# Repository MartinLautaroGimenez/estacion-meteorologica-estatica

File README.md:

# Estación Meteorológica Fija
## ¿Qué es una estación meteorológica?
Una estación meteorológica es un dispositivo tecnológico de características electrónica e informática que permite nuclear parámetros relevantes para realizar estudios y sacar conclusiones frente a fenómenos físicos.

## ¿Qué es E.M.F.?
Este es el inicio del proyecto EME, fue desarrollado en 2022 por el Alumno Nicolas Pérez de la escuela ETec UM, para posteriormente en el año 2024, tras el egreso de Nicolas de la escuela, la estación fue acogida por el taller Aeroglobe ETec y en conjunto con el nevo equipo que se creó en el taller se le pudo dar continuidad y agregar sensores y actualizar partes de la estación. 

## E.M.E.
Este es un proyecto institucional y surge de la necesidad de poder comprar los sistemas atmosféricos de algunos departamentos como Godoy Cruz, Gran Mendoza, Lavalle entre otros departamentos unidos a la red de la Escuela ETec de la Universidad de Mendoza para tener un conocimiento amplio de las condiciones atmosféricas de la provincia y así contribuir al análisis de las condiciones climáticas de la misma. Este es el nexo entre todas las estaciones y su finalidad es crear una red de nodos open surce en la cual podamos extraer datos para diferentes investigaciones o proyectos ya sean de la escuela o externos ya que los datos son públicos.  

## Los modulos incorporados
  - [ESP32](#ESP32)
  - [BMP180](#BMP180)
  - [DHT22](#DHT22)
  - [BMS 3S](#BMS-3S)
  - [Baterías 18650](#Baterías-18650)
  - [Panel Solar](#Panel-Solar)
  - [Sensor de Hoja Mojada](#Sensor-de-Hoja-Mojada)
  - [BH1750](#BH1750)
  - [MQ-135](#MQ-135)
  - [Veleta](#Veleta)
  - [Anemómetro](#Anemómetro)
 
### ESP32
#### DOIT ESP32 Devkit V1
La placa ESP32 (DOIT ESP32 Devkit V1) es un módulo basado en el microcontrolador ESP32, conocido por su capacidad de conexión Wi-Fi y Bluetooth. En nuestra estación meteorológica, esta placa desempeñará un papel vital al ofrecer una base solida para la  recopilación y transmisión de datos ambientales. Con su capacidad para manejar múltiples sensores y su compatibilidad con entornos de desarrollo como Arduino IDE, la ESP32 garantiza un funcionamiento continuo incluso en condiciones adversas, asegurando la integridad y precisión de las mediciones meteorológicas.

<div align="center">
   
</div>

### BMP180
El sensor BMP180 es un dispositivo el cual es utilizado para medir la presión atmosférica y la altitud a nivel del mar con un alto nivel de precisión. Es conocido por su pequeño tamaño y por su simplicidad al momento de realizar mediciones. 

<div align="center">
   
</div>

### DHT22
El sensor DHT22 es un componente crucial en el campo de la electrónica y la monitorización ambiental. 
Su función principal es medir con precisión la temperatura ambiente y la humedad relativa del entorno en el que se encuentra la estación meteorológica. Este sensor incorpora un termistor para la medición de la temperatura y un elemento especializado para medir la humedad relativa.

<div align="center">
   
</div>

### BMS 3S
El módulo BMS 3S es esencial para la carga de las baterías, ya que desempeña un papel crucial en la regulación del voltaje que reciben durante el proceso de carga. Este módulo garantiza que las baterías reciban el voltaje adecuado para una carga segura y eficiente.

<div align="center">
   
</div>

### Baterías 18650
Las baterías 18650 son células recargables de iones de litio conocidas por su alta densidad de energía y fiabilidad. En nuestra estación meteorológica, estas baterías desempeñarán un papel vital al ofrecer una fuente de alimentación constante y duradera, lo que garantizará un funcionamiento continuo incluso en condiciones adversas en las que el panel solar no pueda suministrar la potencia nominal.

<div align="center">
   
</div>

### Panel Solar
El panel solar le da la capacidad de poder estar lejos en un sector en donde no sea posible el tendido eléctrico para la alimentación de la EME, además brinda una opción de energía sustentable y limpia, reduciendo así el consumo eléctrico convencional que mayoritariamente proviene de centrales térmicas.
Además el mismo se le incorpora un pequeño módulo regulador de tensión para poder adaptar los niveles de tensión requeridos para la lógica del microcontrolador.

<div align="center">
   
</div>

### Sensor de Hoja Mojada
El sensor de hoja mojada permite tomar cómo parámetro el estado de la planta en cuanto a la generación de microorganismos que se presenten en la planta, de está manera se puede regular la aplicación de insecticida sin sobredosificar y ahorrando cantidades del mismo, si el mismo fuese aplicado a calendario. Además permite tener un mejor control en cuanto a la biodiversidad de los demás microorganismos que puedan aparecer en la planta que no sean dañinos. 

<div align="center">
   
</div>

### BH1750
El sensor BH1750 es un sensor el cual está diseñado para medir la intensidad de la luz de manera precisa. Es altamente valorado por su facilidad de uso y su capacidad de obtener lecturas rápidas en una amplia variedad de ambientes. Su pequeño tamaño y alta precisión lo hacen el más querido de los sensores de luz.

<div align="center">
   
</div>

### MQ-135
El sensor MQ135 es un componente el cual permite detectar gases nocivos para el aire, como el amoníaco, sulfuro de hidrógeno, dióxido de carbono, y otros compuestos orgánicos volátiles. Es conocido por la capacidad de proporcionar alertas tempranas sobre la presencia de estos gases.
De este sensor podemos tomar datos analógicos del comportamiento de la mezcla de gases y la capacidad de marcar un umbral de disparo para una salida digital de ser requerida, para ello es necesario acceder manualmente al trimmer de su pcb y calibrar el disparo del mismo

<div align="center">
   
</div>

### Veleta
Permite tomar la dirección actual del viento discretizando dicha dirección en 8 posiciones cardinales gracias a su forma constructiva, un imán de neodimio y 8 reed switch.

<div align="center">
     
</div>

### Anemómetro 
Para el anemómetro se requiere tanto de la parte física como del módulo o sensor de efecto hall que es quien detecta cada revolución de giro y la envía a una etapa amplificadora para poder contar cada pulso entrante 

<div align="center">
    
</div>

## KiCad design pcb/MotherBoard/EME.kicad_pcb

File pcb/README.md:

# Circuito
Para el diseño del proyecto, concretamente para la parte electrónica de diseño de PCB se a optado por usar un software libre y poderoso llamado KiCAD en su versión número 7 con la integración de una librería casera tanto el símbolo esquemático cómo la huella (footprint) del PCB.

# Diagrama esquemático

Para el diagrama 

# Diseño de la PCB

Para el Diseño de la PCB

# Modelo 3D

Para el modelo 3D

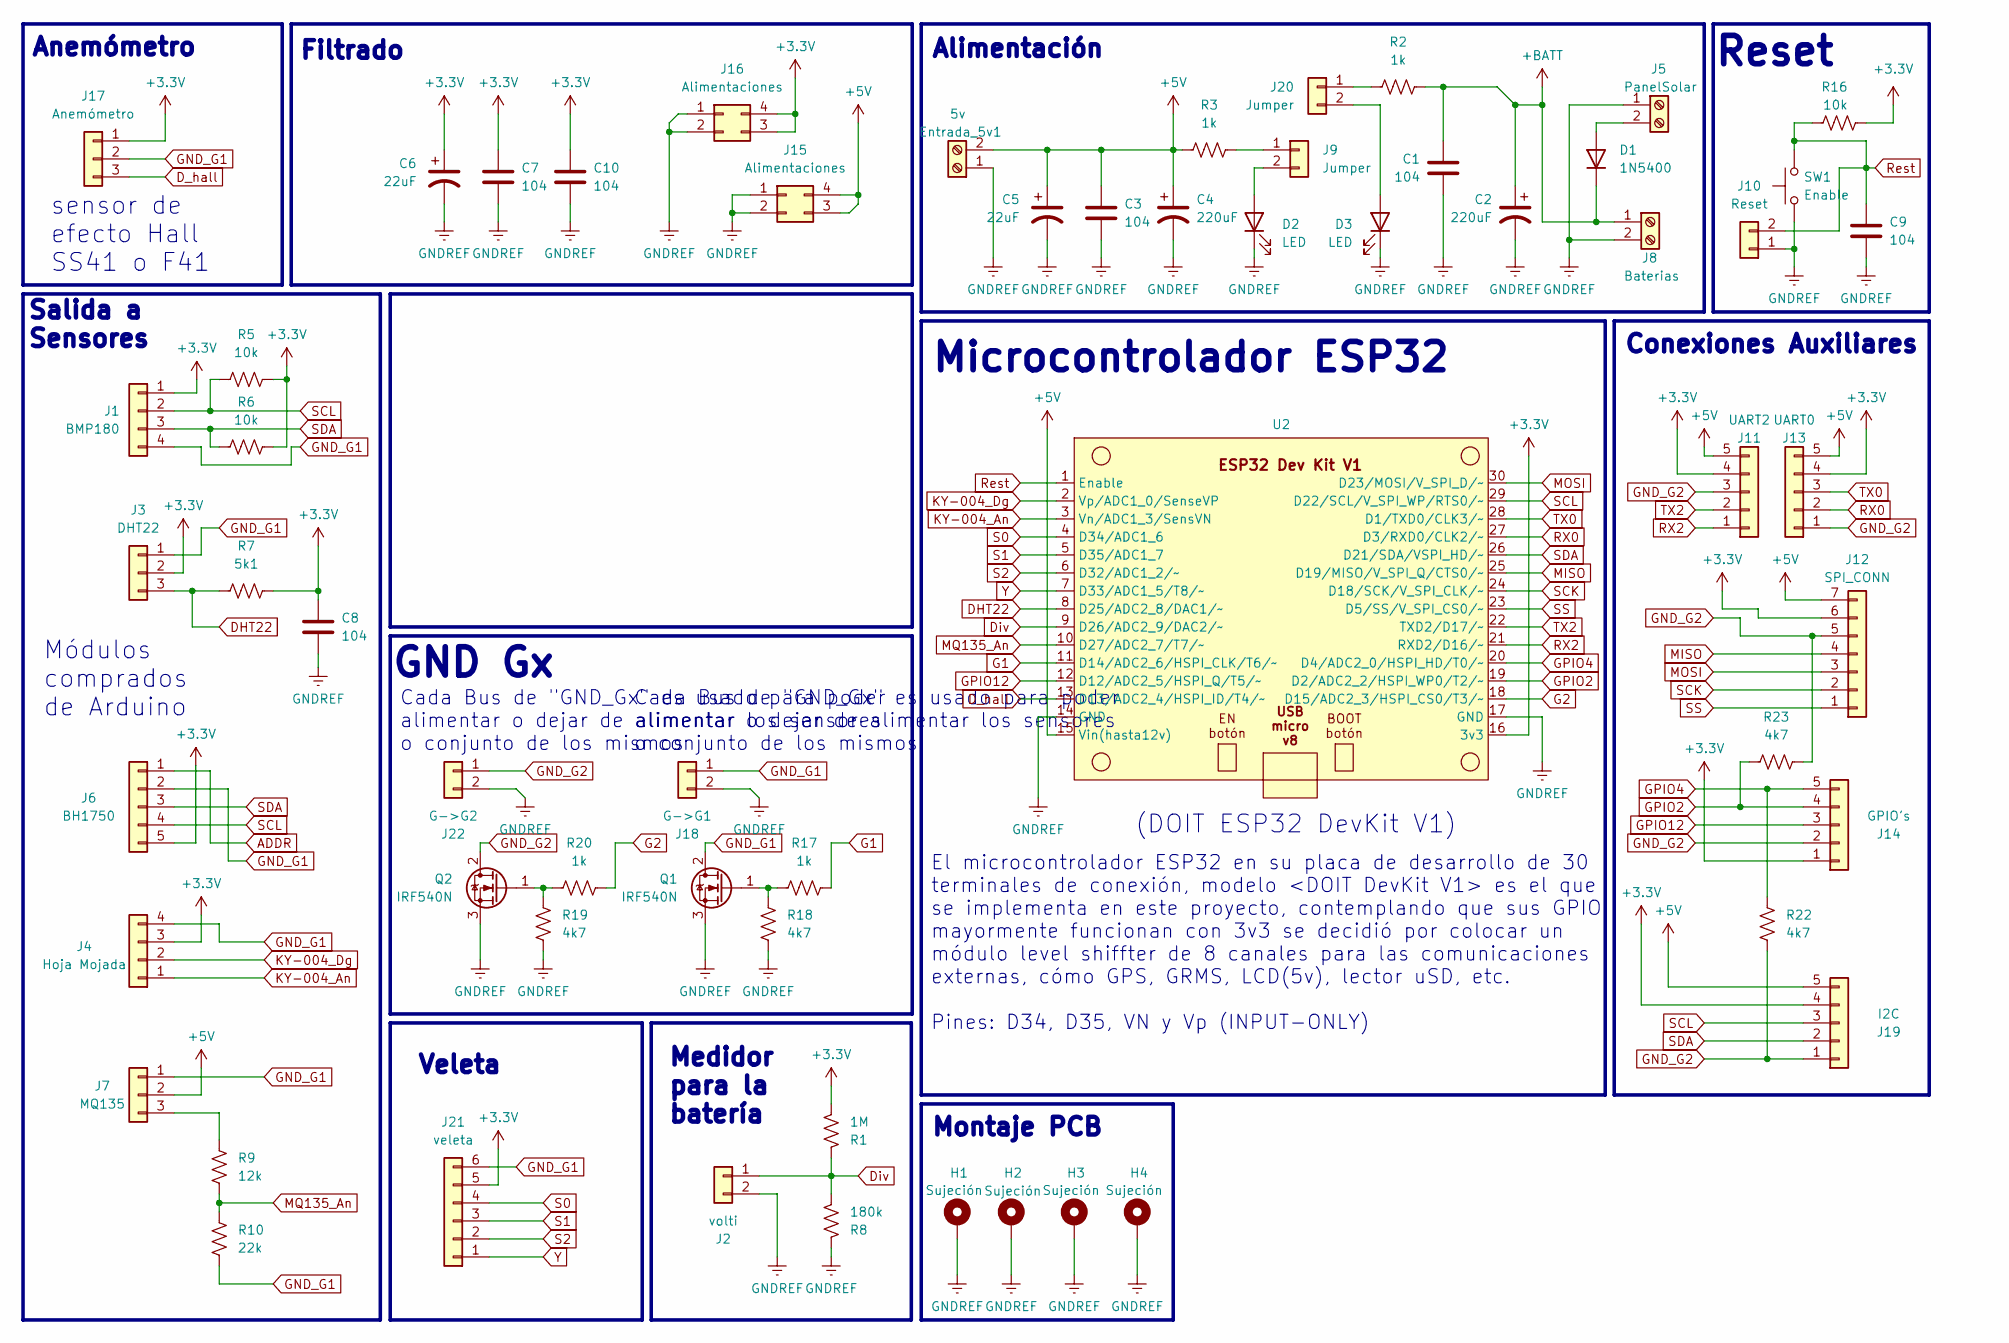
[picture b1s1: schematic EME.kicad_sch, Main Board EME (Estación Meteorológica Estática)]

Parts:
C1, C3, C7, C10: 104; C_Disc_D7.0mm_W2.5mm_P5.00mm
C2, C4: 220uF; C_Radial_D8.0mm_H11.5mm_P3.50mm
C5, C6: 22uF; C_Radial_D8.0mm_H7.0mm_P3.50mm
C8: 104; C_Disc_D7.5mm_W4.4mm_P5.00mm
C9: 104; C_Disc_D4.3mm_W1.9mm_P5.00mm
D1: 1N5400; D_DO-201AD_P15.24mm_Horizontal
D2, D3: LED; LED_D5.0mm_Clear
Entrada_5v1: 5v; TerminalBlock_Phoenix_PT-1,5-2-5.0-H_1x02_P5.00mm_Horizontal
H1, H2, H3, H4: Sujeción; MountingHole_3.5mm_Pad
J1: BMP180; PinHeader_1x04_P2.54mm_Vertical
J2: volti; PinHeader_1x02_P2.54mm_Vertical
J3: DHT22; PinHeader_1x03_P2.54mm_Vertical
J4: Hoja Mojada; PinHeader_1x04_P2.54mm_Vertical
J5: PanelSolar; TerminalBlock_Phoenix_PT-1,5-2-5.0-H_1x02_P5.00mm_Horizontal
J6: BH1750; PinHeader_1x05_P2.54mm_Vertical
J7: MQ135; PinHeader_1x03_P2.54mm_Vertical
J8: Baterias; TerminalBlock_Phoenix_PT-1,5-2-5.0-H_1x02_P5.00mm_Horizontal
J9, J20: Jumper; PinHeader_1x02_P2.54mm_Vertical
J10: Reset; PinHeader_1x02_P2.54mm_Vertical
J11: UART2; PinHeader_1x05_P2.54mm_Vertical
J12: SPI_CONN; PinHeader_1x07_P2.54mm_Vertical
J13: UART0; PinHeader_1x05_P2.54mm_Vertical
J14: GPIO's; PinHeader_1x05_P2.54mm_Vertical
J15, J16: Alimentaciones; PinHeader_2x02_P2.54mm_Vertical
J17: Anemómetro; PinHeader_1x03_P2.54mm_Vertical
J18: G->G1; PinHeader_1x02_P2.54mm_Vertical
J19: I2C; PinHeader_1x05_P2.54mm_Vertical
J21: veleta; PinHeader_1x06_P2.54mm_Vertical
J22: G->G2; PinHeader_1x02_P2.54mm_Vertical
Q1, Q2: IRF540N; TO-220-3_Vertical
R1: 1M; R_Axial_DIN0207_L6.3mm_D2.5mm_P10.16mm_Horizontal
R2, R3, R17, R20: 1k; R_Axial_DIN0207_L6.3mm_D2.5mm_P10.16mm_Horizontal
R5, R6, R16: 10k; R_Axial_DIN0207_L6.3mm_D2.5mm_P10.16mm_Horizontal
R7: 5k1; R_Axial_DIN0207_L6.3mm_D2.5mm_P10.16mm_Horizontal
R8: 180k; R_Axial_DIN0207_L6.3mm_D2.5mm_P10.16mm_Horizontal
R9: 12k; R_Axial_DIN0207_L6.3mm_D2.5mm_P10.16mm_Horizontal
R10: 22k; R_Axial_DIN0207_L6.3mm_D2.5mm_P10.16mm_Horizontal
R18, R19, R22, R23: 4k7; R_Axial_DIN0207_L6.3mm_D2.5mm_P10.16mm_Horizontal
SW1: Enable; SW_PUSH_6mm_H8mm
U2: ESP32-DevKit_V1

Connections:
+3.3V: C6.1, C7.1, C8.1, C10.1, J1.1, J3.2, J4.3, J6.5, J11.4, J12.6, J13.4, J14.1, J16.3, J16.4, J17.1, J19.4, J21.5, R1.1, R5.2, R6.2, R7.2, R16.2, U2.16 (3v3); also elsewhere on the board
+5V: C3.1, C4.1, C5.1, Entrada_5v1.2, J7.2, J11.5, J12.7, J13.5, J15.3, J15.4, J19.5, R3.1, U2.15 (Vin(hasta12v))
+BATT: C1.1, C2.1, D1.1 (K), J8.1, R2.2
ADDR: J6.1
DHT22: J3.3, R7.1, U2.8 (D25/ADC2_8/DAC1/~)
D_hall: J17.3, U2.13 (D13/ADC2_4/HSPI_ID/T4/~)
Div: J2.1, R1.2, R8.1, U2.9 (D26/ADC2_9/DAC2/~)
G1: R17.2, U2.11 (D14/ADC2_6/HSPI_CLK/T6/~)
G2: R20.2, U2.18 (D15/ADC2_3/HSPI_CS0/T3/~)
GNDREF: C1.2, C2.2, C3.2, C4.2, C5.2, C6.2, C7.2, C8.2, C9.2, C10.2, D2.1 (K), D3.1 (K), Entrada_5v1.1, H1.1, H2.1, H3.1, H4.1, J2.2, J5.1, J8.2, J10.1, J15.1, J15.2, J16.1, J16.2, J18.2, J22.2, Q1.3 (S), Q2.3 (S), R8.2, R18.1, R19.1, SW1.1, U2.14 (GND), U2.17 (GND); also elsewhere on the board
GND_G1: J1.4, J3.1, J4.4, J6.2, J7.1, J17.2, J18.1, J21.6, Q1.2 (D), R10.1
GND_G2: J11.3, J12.5, J13.1, J14.2, J19.1, J22.1, Q2.2 (D), R22.1, R23.1
GPIO2: J14.4, R23.2, U2.19 (D2/ADC2_2/HSPI_WP0/T2/~)
GPIO4: J14.5, R22.2, U2.20 (D4/ADC2_0/HSPI_HD/T0/~)
GPIO12: J14.3, U2.12 (D12/ADC2_5/HSPI_Q/T5/~)
KY-004_An: J4.1, U2.3 (Vn/ADC1_3/SensVN)
KY-004_Dg: J4.2, U2.2 (Vp/ADC1_0/SenseVP)
MISO: J12.4, U2.25 (D19/MISO/V_SPI_Q/CTS0/~)
MOSI: J12.3, U2.30 (D23/MOSI/V_SPI_D/~)
MQ135_An: R9.1, R10.2, U2.10 (D27/ADC2_7/T7/~)
unnamed: D1.2 (A), J5.2
unnamed: D2.2 (A), J9.2
unnamed: D3.2 (A), J20.2
unnamed: J7.3, R9.2
unnamed: J9.1, R3.2
unnamed: J20.1, R2.1
unnamed: Q1.1 (G), R17.1, R18.2
unnamed: Q2.1 (G), R19.2, R20.1
RX0: J13.2, U2.27 (D3/RXD0/CLK2/~)
RX2: J11.1, U2.21 (RXD2/D16/~)
Rest: C9.1, J10.2, R16.1, SW1.2, U2.1 (Enable)
S0: J21.4, U2.4 (D34/ADC1_6)
S1: J21.3, U2.5 (D35/ADC1_7)
S2: J21.2, U2.6 (D32/ADC1_2/~)
SCK: J12.2, U2.24 (D18/SCK/V_SPI_CLK/~)
SCL: J1.2, J6.4, J19.3, R5.1, U2.29 (D22/SCL/V_SPI_WP/RTS0/~)
SDA: J1.3, J6.3, J19.2, R6.1, U2.26 (D21/SDA/VSPI_HD/~)
SS: J12.1, U2.23 (D5/SS/V_SPI_CS0/~)
TX0: J13.3, U2.28 (D1/TXD0/CLK3/~)
TX2: J11.2, U2.22 (TXD2/D17/~)
Y: J21.1, U2.7 (D33/ADC1_5/T8/~)

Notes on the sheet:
Cada Bus de "GND_Gx" es usado para poder alimentar o dejar de alimentar los sensores o conjunto de los mismos
Salida a Sensores
GND Gx
Anemómetro
sensor de efecto Hall SS41 o F41
El microcontrolador ESP32 en su placa de desarrollo de 30 terminales de conexión, modelo <DOIT DevKit V1> es el que se implementa en este proyecto, contemplando que sus GPIO mayormente funcionan con 3v3 se decidió por colocar un módulo level shiffter de 8 canales para las comunicaciones externas, c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
Microcontrolador ESP32
Medidor para la batería
Veleta
Módulos comprados de Arduino
Reset
Alimentación
Montaje PCB
Filtrado
(DOIT ESP32 DevKit V1)
Conexiones Auxiliares

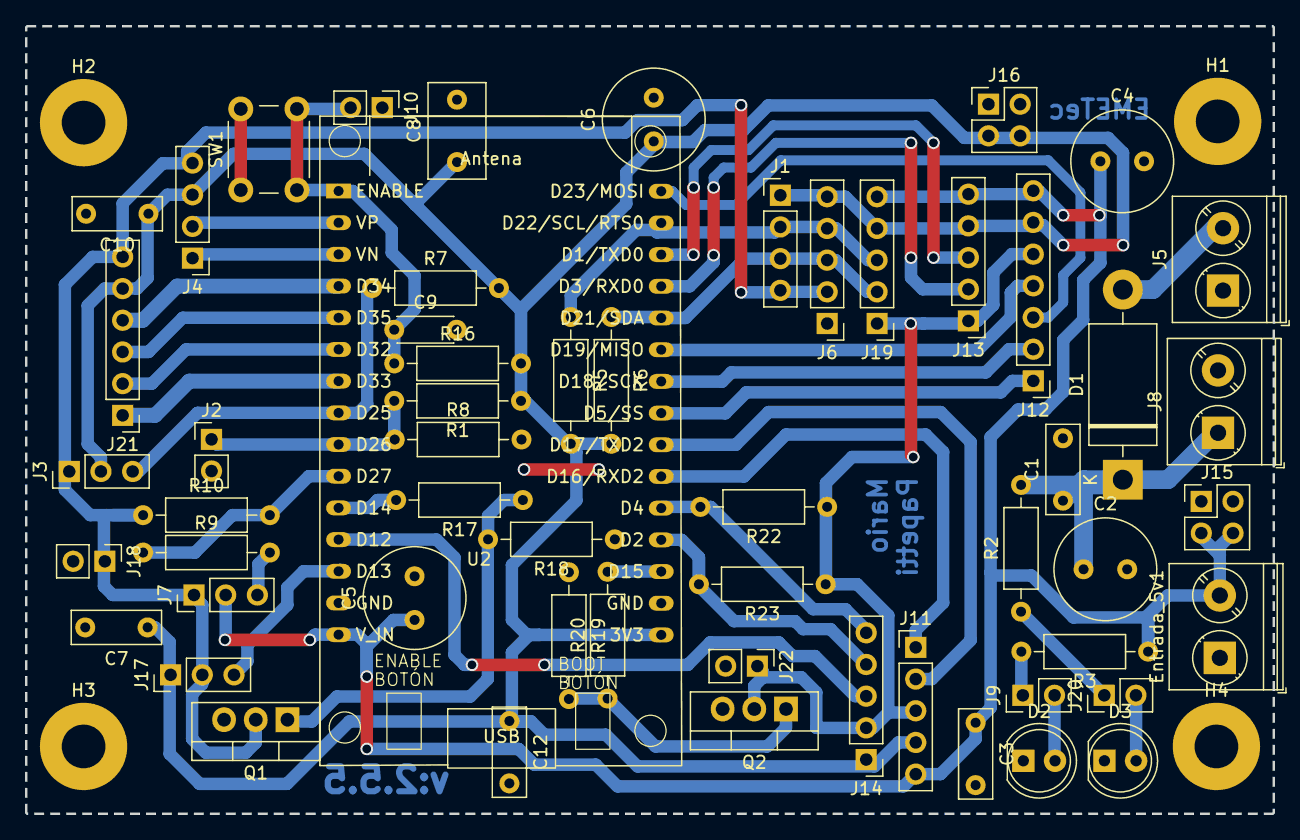
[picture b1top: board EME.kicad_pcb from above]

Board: 2 copper layers, 100.0 x 63.1 mm, 61 parts (0 on the bottom side), 40 nets.

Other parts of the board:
C12: 104; C_Disc_D7.0mm_W2.5mm_P5.00mm

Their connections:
+3.3V: C12.1; also elsewhere on the board
GNDREF: C12.2; also elsewhere on the board

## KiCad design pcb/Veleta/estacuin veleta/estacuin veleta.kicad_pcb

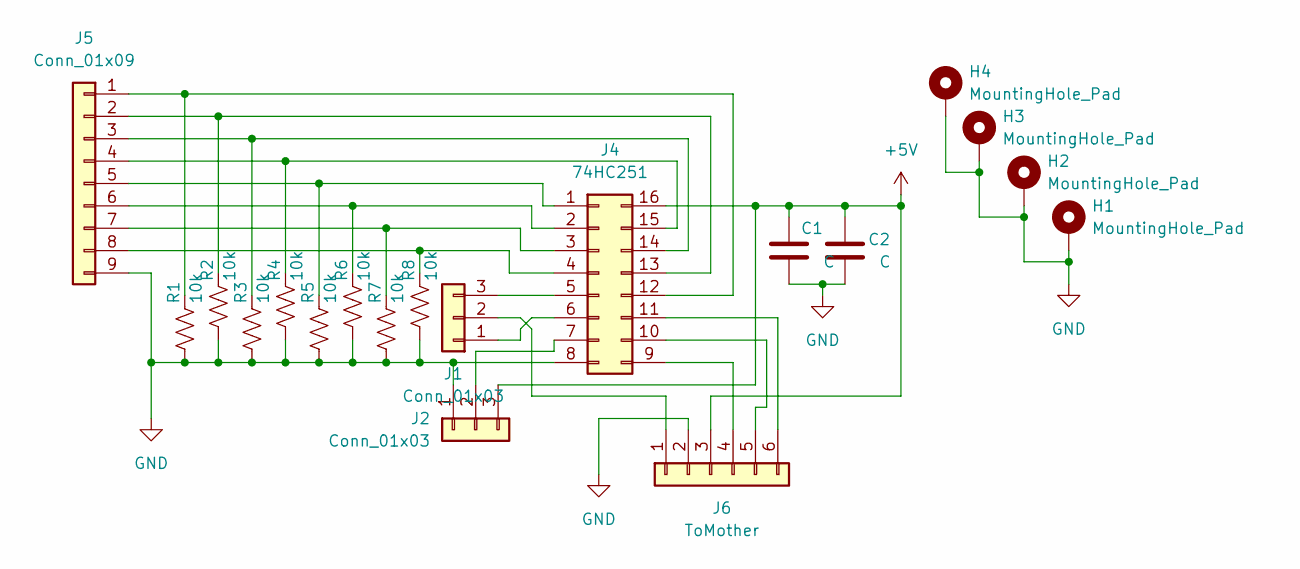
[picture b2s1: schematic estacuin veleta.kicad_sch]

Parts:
C1, C2: C; C_Radial_D6.3mm_H7.0mm_P2.50mm
H1, H2, H3, H4: MountingHole_Pad; MountingHole_2.2mm_M2_DIN965_Pad
J1, J2: Conn_01x03; PinHeader_1x03_P2.54mm_Vertical
J4: 74HC251; DIP-16_W7.62mm
J5: Conn_01x09; PinSocket_1x09_P2.54mm_Vertical
J6: ToMother; PinSocket_1x06_P2.54mm_Vertical
R1, R2, R3, R4, R5, R6, R7, R8: 10k; R_Axial_DIN0207_L6.3mm_D2.5mm_P10.16mm_Horizontal

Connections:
+5V: C1.1, C2.1, J2.3, J4.16, J6.3
GND: C1.2, C2.2, H1.1, H2.1, H3.1, H4.1, J2.1, J4.8, J5.9, J6.2, R1.2, R2.2, R3.2, R4.2, R5.2, R6.2, R7.2, R8.2
unnamed: J1.1, J4.6
unnamed: J1.2, J6.1
unnamed: J1.3, J4.5
unnamed: J2.2, J4.7
unnamed: J4.1, J5.5, R5.1
unnamed: J4.2, J5.6, R6.1
unnamed: J4.3, J5.7, R7.1
unnamed: J4.4, J5.8, R8.1
unnamed: J4.9, J6.4
unnamed: J4.10, J6.5
unnamed: J4.11, J6.6
unnamed: J4.12, J5.1, R1.1
unnamed: J4.13, J5.2, R2.1
unnamed: J4.14, J5.3, R3.1
unnamed: J4.15, J5.4, R4.1

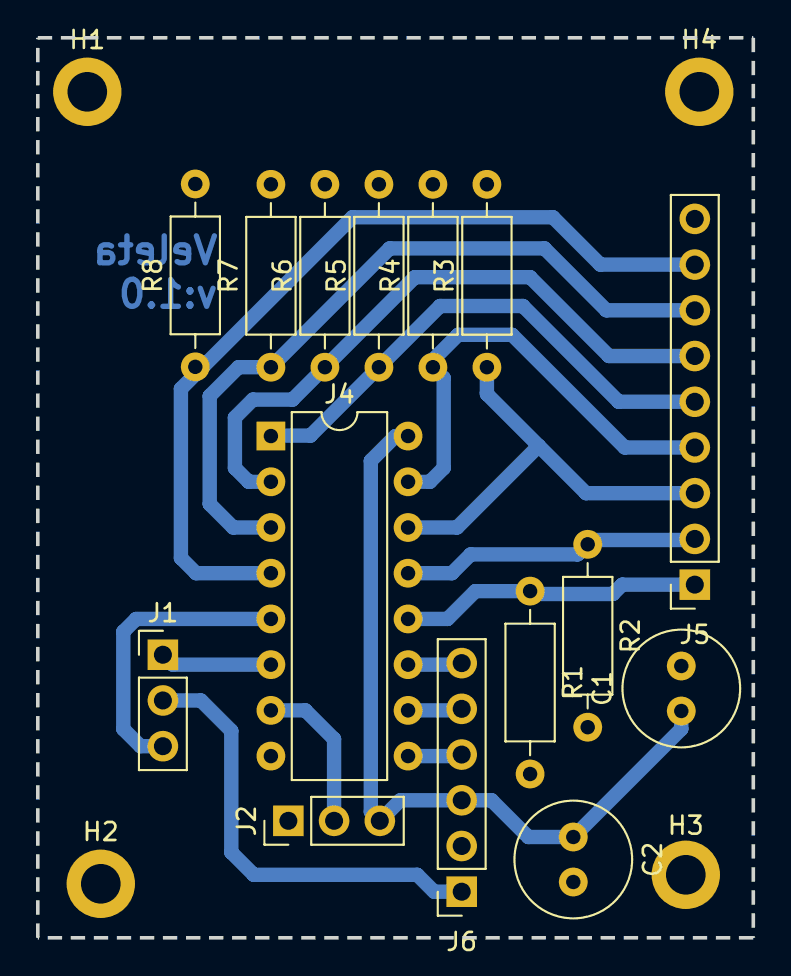
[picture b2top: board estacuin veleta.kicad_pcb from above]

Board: 2 copper layers, 39.8 x 50.0 mm, 19 parts (0 on the bottom side), 17 nets.

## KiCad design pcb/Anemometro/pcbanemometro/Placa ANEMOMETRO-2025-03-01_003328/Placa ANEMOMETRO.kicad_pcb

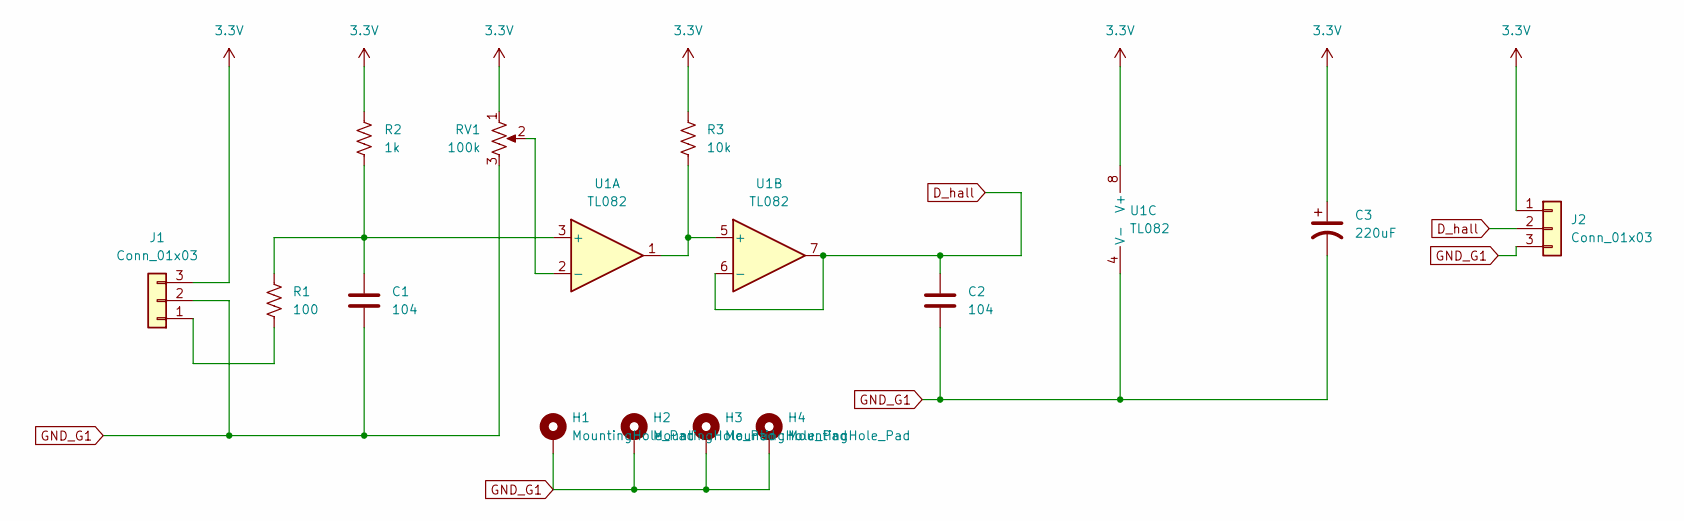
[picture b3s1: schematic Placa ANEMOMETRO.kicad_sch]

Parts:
C1, C2: 104; C_Disc_D4.3mm_W1.9mm_P5.00mm
C3: 220uF; C_Radial_D5.0mm_H7.0mm_P2.00mm
H1, H2, H3, H4: MountingHole_Pad; MountingHole_2.2mm_M2_DIN965_Pad
J1, J2: Conn_01x03; PinHeader_1x03_P2.54mm_Vertical
R1: 100; R_Axial_DIN0207_L6.3mm_D2.5mm_P7.62mm_Horizontal
R2: 1k; R_Axial_DIN0207_L6.3mm_D2.5mm_P7.62mm_Horizontal
R3: 10k; R_Axial_DIN0207_L6.3mm_D2.5mm_P7.62mm_Horizontal
RV1: 100k; Potentiometer_Bourns_3296Y_Vertical
U1: TL082; DIP-8_W7.62mm_Socket

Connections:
3.3V: C3.1, J1.3, J2.1, R2.1, R3.1, RV1.1, U1.8 (V+)
D_hall: C2.1, J2.2, U1.6 (-), U1.7
GND_G1: C1.2, C2.2, C3.2, H1.1, H2.1, H3.1, H4.1, J1.2, J2.3, RV1.3, U1.4 (V-)
unnamed: J1.1, R1.2
unnamed: C1.1, R1.1, R2.2, U1.3 (+)
unnamed: RV1.2, U1.2 (-)
unnamed: R3.2, U1.1, U1.5 (+)

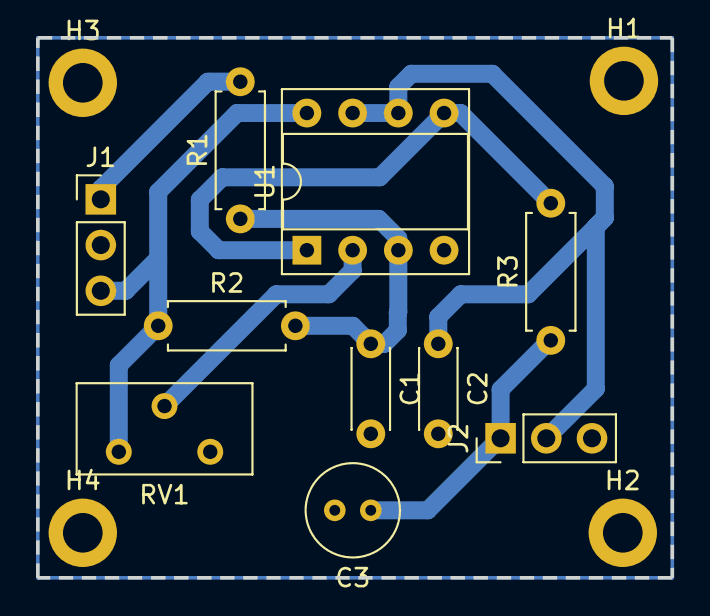
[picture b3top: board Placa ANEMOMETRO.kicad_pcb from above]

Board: 2 copper layers, 35.2 x 30.0 mm, 14 parts (0 on the bottom side), 7 nets.

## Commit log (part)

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2024-03-07 Se añadió nodejs y se añadio un ejemplar de conexion a una db local (mysql)
2024-04-22 Se agregó diseño3D y PCB v0.1
2024-04-23 Se convirtió la web anterior a una de nodejs.
2024-05-07 se agregaron ejemplos de los sensores y actualizo la PCB
2024-05-10 Se movió la carpeta de ejemplos para mejor funcionamiento de PIO. Se añadieron/modificaron ejemplos de bmp180, bh170, dht22
2024-05-10 Un commmit para hacer pull en la mario pc :v
2024-05-11 Se modificó el platformio y el main.cpp
2024-06-14 Se añadieron algunos codigos sobre los sensores.
2024-06-17 Refactorizar código de sensores y ejemplos
2024-06-17 Se armó diseño de PCB y se decoró esquemático
2024-06-17 Se avanzó con los programas de ejemplo de Anemómetro y Veleta, falta verificarlos en simulador
2024-06-17 se han agregado los readmes a cada carpeta relevante, además de fotos de lo de kicad
2024-06-17 se reformatearon los readme.md
2024-07-07 Se rehizo completamente el sistema de visualización web. Se encuentra funcional
2024-08-04 se agregó código de mainSource que es el prototipo funcional v0.2 de la EME
2024-08-04 se agregó archivo config.h para seguridad
2024-08-04 se espejó y adapto la librería LeerSensores que funciona en la EMM, queda revisar por 3ro
2024-08-04 Se realizaron cambios en la web
2024-08-06 se intentó agregar deepSleep fallidamente, revisar porque quedó con un delay re chunfle
2024-08-07 se actualizó el envío de datos por mqtt de forma más ordenada
2024-08-07 se arregló el envío de data que estaba mal las unidades
2024-08-11 se ha excluido backup de pcb
2024-08-11 se a omitido los backups de pcb
2024-08-11 Se corrigieron errores de la web.
2024-08-11 se modificó el readme de la web
2024-08-15 Changes to be committed: new file: .gitignore deleted: Src/main.c modified: Src/mainSource/platformio.ini new file: Web/Node-Red/Flow_releaseV0(13-08-24).json modified: Web/graphics.js new file: pcb/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
2024-09-03 Se añadió el codigo de ejemplo RTC. Se empezó con lo solicitado en la parte web.
2024-09-29 Refactorizar código para agregar funcionalidad de selección de categoría en la parte web
2024-09-29 correcciones minimas de funcionamiento
2024-10-02 Se corrigió el tiempo que demora en enviar los datos.
2024-10-02 Se volvi{o a una version anterior de app.js
2024-10-11 Cambios minimos
2024-10-11 Test
2024-10-23 ffw4420 9fsr ed
2024-10-27 se actualizó la PCB
2024-10-30 Se empezó a administrar control mosfet
2024-11-01 Se empezó a administrar la api rest
2024-11-01 Cambios dropdown
2024-11-01 Dropdown para pruebas activado parcialmente
2024-11-01 Se corrigió la visualización del último dato
2024-11-02 Cambios en el dropdown: Se le añadio Test a la pestaña Datos, y se configuró una cookie
2024-11-02 Añadido URLs de API para la gestión de datos en el archivo app.js
2024-11-02 Añadidas funciones para gestionar cookies y descargar datos en XLSX según la selección del dropdown
2024-11-02 Añadidas variables para las URLs de las APIs en excel.js y actualizada la función de descarga para usar estas variables según la categoría seleccionada
2024-11-02 Actualizada la documentación del README.md para incluir descripciones detalladas del Dashboard. Se mejoró la interfaz de usuario en index.html añadiendo estilo de cursor a las imágenes de perfil. Se 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
2024-11-02 Añadido test http a través. Se incluye la configuración de conexión Wi-Fi y se aumenta el tamaño del buffer para el mensaje JSON. Se agrega la dependencia HTTPClient en platformio.ini.
2024-11-04 se actualizó la PCB y se avanzó con el código main
2024-11-07 avances de main.cpp
2024-11-09 update main
2024-11-10 se agregó función de encendido de MOSFET, posibilidad de elección entre diversos DHT's y se agregaron etiquetas de funciones
2024-11-12 main updated
2024-11-13 se agregaron hojas de datos de componetes eletrónicos relevantes
2024-11-14 Corregidas descripciones de estudiantes en index.html para incluir "de la ETec" y añadido nuevo integrante al equipo.
2024-11-16 Cambios
2024-11-18 Actualizar URL de la API de la EMM en app.js
2024-11-18 Create Gaseta
2024-11-18 Gaseta
2024-11-18 se actualizaron los pines de conexión
2024-11-18 Actualizar URLs de las APIs en excel.js
2024-11-19 Se actualizó PCB y se agregó funcionalidad de sensor lluvia, veleta y anemómetro
2024-11-19 se agregó funcionalidad correcta del anemometro
2024-11-28 Nuevo BK de Node-Red
2024-12-04 Se agregó estilo personalizado para elementos select y opciones en CSS
2024-12-06 Cambios en microcontrolador
2024-12-06 OTA test 1
2024-12-07 Agregar opción 'emm3' en el dropdown de nodos meteorológicos
2024-12-07 Test of "No disponible"
2024-12-07 Mejorar manejo de datos nulos en la función obtenerDatos
2024-12-07 Agregar opción 'emm3' en la función de descarga de datos y definir la URL correspondiente
2024-12-07 Actualizar URL de API y optimizar la obtención de datos en gráficos; agregar opción 'emm3' en el dropdown de nodos meteorológicos
2024-12-07 Actualizar la inclusión de scripts en graphs.html para usar la nueva URL de graphics.js
2024-12-07 Eliminar el dropdown de selección de nodos meteorológicos en graphs.html
2024-12-07 Cambio de nombre de EMM Malargüe
2024-12-10 Se añadió el nodo del Luis
2024-12-10 Se terminó de añadir el nodo del luis
2024-12-10 Actualizar datos.html y excel.js: renombrar variables y ajustar inclusión de scripts
2024-12-10 Actualizar datos.html: ajustar inclusión de scripts para excel.js
2024-12-10 Renombrar variables de API en excel.js para evitar conflictos
2025-02-26 Añadir soporte para el nodo "Colegio San Jorge" en la selección de categorías y actualizar las URLs de la API en excel.js
2025-02-26 Actualizar el valor del nodo "Colegio San Jorge" en datos.html
2025-02-26 Eliminar margen derecho del dropdown en datos.html
2025-02-26 Actualizar el formato de la altitud en app.js para incluir "mts"
2025-02-28 Nueva versión de la PCB, se saca a parte veleta y anemómetro en placas aparte con los sensores
2025-02-28 Agregada carpetas para PCBs
2025-03-01 Actualizar la configuración de PlatformIO y mejorar el controlador WiFi eliminando código redundante y ajustando la implementación del servidor web cautivo. Deepsleep mediante post.
2025-03-02 Actualizar la configuración de PlatformIO y eliminar código redundante en LeerSensores. Agregar funcionalidad para eliminar credenciales WiFi.
2025-03-02 se readaptaron y revisaron las PCBs, listas para imprimir
2025-03-18 Agregar controlador WiFi con portal cautivo y eliminar implementación anterior. Actualizar dependencias en platformio.ini.
2025-03-18 Agregar archivo de configuración de PlatformIO y archivos de bloqueo para la PCB.
2025-03-19 Actualizar configuración de VSCode, agregar biblioteca DHT y mejorar manejo de valores nulos en la interfaz web.
2025-03-19 Actualizar referencia de script en index.html y descomentar script de emetec
2025-03-19 Mejorar manejo de valores nulos en la función obtenerValor para incluir -1 como valor no disponible.
2025-04-01 Eliminar archivos de compilación y actualizar la configuración de .gitignore para excluir la carpeta .pio
2025-04-01 Mejorar la función obtenerValor para simplificar el manejo de valores nulos y negativos.
2025-04-04 Se agregó la modificación del MQ135 a 5v con divisor resistivo; además de cambio del DHT del pin 12; también se modificaron los pines de conexión
2025-04-13 Agregar archivos de configuración y nuevas páginas HTML, eliminar archivos innecesarios y actualizar .gitignore
2025-04-13 Actualizar .gitignore para incluir la carpeta Web/old y eliminar la entrada de em
2025-04-13 Corregir la ruta del archivo CSS en datos.html para asegurar la carga correcta del estilo
2025-04-13 Actualizar rutas de archivos CSS y JS en index.html para asegurar la carga correcta de los estilos y scripts
2025-04-14 Eliminar archivo datos.xlsx y agregar funcionalidad para verificar el estado del nodo en datos.html y back.js
2025-04-14 Actualizar ruta del archivo CSS en datos.html para utilizar style_au.css
2025-04-14 Actualizar rutas de archivos CSS en about_us.html y datos.html para corregir la carga de estilos
2025-04-14 Actualizar ruta del archivo CSS en about_us.html para corregir el nombre del archivo
2025-04-14 Actualizar ruta del archivo CSS en about_us.html para utilizar style.css
2025-04-14 Agregar estilos para la tarjeta de estado del nodo y colores dinámicos según el estado
2025-04-14 Agregar estilos dinámicos para el estado de la tarjeta en datos.html y eliminar estilos redundantes de style.css
2025-04-15 Agregar soporte para OTA y portal cautivo, incluyendo manejo de credenciales WiFi y mejoras en la interfaz
2025-04-23 Agregar impresión de la dirección MAC del ESP32 en la configuración y crear prueba para mostrarla
2025-04-23 pcb review
2025-04-24 Agregar cálculo del índice de calor en la lectura de sensores y mejorar la conexión HTTP en el cliente
2025-04-25 revisión de pcb
2025-04-25 se arregló el funcionamiento de los mosfet y la lectura del MQ135, falta ver porque se no deja resetearse
2025-04-25 Agregar nuevas dependencias para el servidor web asíncrono y la exportación de datos en formato XLSX; incluir documentación inicial del dashboard.
2025-04-25 Actualizar rutas de archivos en la configuración de lanzamiento para entornos de desarrollo en Linux
2025-05-16 Actualizar .gitignore y mejorar la gestión de sensores en el código; eliminar archivo de bloqueo de KiCad.
2025-05-20 "se modificó conexión del DHT22 a otro pin, se agregó jumper G-g1 y g2, también conectores para extraer alimentación"
2025-05-20 se agregaron los pdfs para imprimir las pcbs
2025-06-26 Add PantallaController for LCD display management
    - Created header file pantallacontroller.h to define the PantallaController class with methods for displaying various information on an LCD.
    - Implemented pantallacontroller.cpp to provide functionality for initializing the LCD, displaying welcome messages, sensor readings, WiFi status, and error messages.
    - Added .gitignore to exclude build and configuration files.
    - Introduced extensions.json for VSCode to recommend necessary extensions for the project.
2025-06-28 Refactor lógica de obtención y visualización de datos en back.js; actualizar dropdown en datos.html e index.html
2025-06-28 Actualizar IDs de elementos en index.html para reflejar cambios en la gestión de datos; renombrar popups y ajustar referencias de fecha.
2025-06-28 Refactor back.js para mejorar la legibilidad y optimizar la lógica de obtención de datos; actualizar index.html para corregir IDs y mejorar la estructura del código.
2025-06-28 Refactor back.js para mejorar la lógica de carga de datos según la selección del dropdown; optimizar la verificación del estado del nodo y simplificar la normalización de valores.
2025-06-29 Refactor back.js para simplificar la obtención de datos y mejorar la visualización; actualizar index.html para corregir IDs de fechas.
2025-06-29 Actualizar la referencia a back.js en index.html y datos.html para evitar el almacenamiento en caché.
2025-06-30 Agregar WebController para gestionar la interfaz web y la comunicación de datos; implementar rutas HTTP y lógica de presentación.
2025-06-30 Add lock file for EME.kicad_pcb to track editing session
2025-06-30 Actualizar la visualización de datos: cambiar la unidad de CO2 a Ω y renombrar el encabezado a "Gases Volátiles".
2025-06-30 Actualizar la unidad de CO2 a KΩ en la visualización de datos
2025-06-30 Actualizar el encabezado de "Gases Volátiles" a "Gases Volátiles (Resistencia)" en datos.html
2025-06-30 Actualizar la lógica de calidad del aire y ajustar la carga de scripts en HTML; agregar configuración de Live Server.
2025-08-08 Dato calidad del aire
2025-08-08 Arreglo dato aire (ahora sí)
2025-08-12 Actualizar scripts de carga y ocultar elementos adicionales en HTML
2025-09-05 Agregar opción para EMM Lavalle 2025 en dropdown y actualizar la lógica de obtención de datos
2025-09-05 Actualizar versión de scripts front y back en HTML
2025-09-06 Agregar página de Estaciones Móviles y actualizar estilos y scripts relacionados
2025-09-12 Avances en Next.js
2025-09-14 Admin panel (mediante filesystem)
2025-10-17 Base de datos
2025-10-17 Pasaje a Next y dashboard terminado
2025-10-26 Primera versión mapa
